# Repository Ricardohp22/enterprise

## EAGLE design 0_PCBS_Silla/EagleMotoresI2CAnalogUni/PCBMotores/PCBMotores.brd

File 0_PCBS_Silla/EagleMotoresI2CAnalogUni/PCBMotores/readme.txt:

PCB Motores - Estatus: Completo
----------------
-Control de motores con sabertooth salidas analógicas

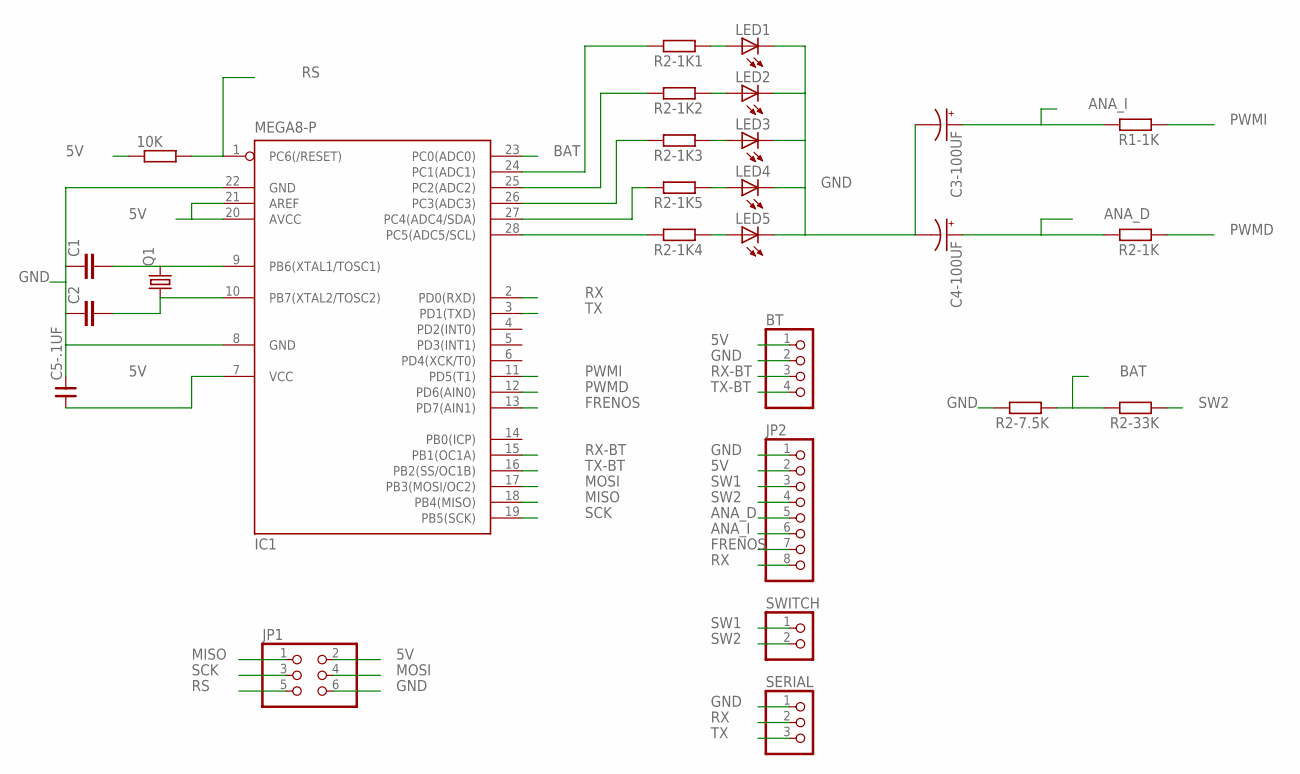
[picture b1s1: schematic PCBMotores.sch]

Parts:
10K: R-EU_0204/7; 0204/7
BT: PINHD-1X4; 1X04
C1, C2: C2.5/5; C2.5-5
C3-100UF, C4-100UF: CPOL-USE2-4; E2-4
C5-.1UF: CNP-C035-055X025; C035-055X025
IC1: MEGA8-P; DIL28-3
JP1: PINHD-2X3; 2X03
JP2: PINHD-1X8; 1X08
LED1, LED2, LED3, LED4, LED5: LED5MM
Q1: CRYSTALHC49S; HC49/S
R1-1K, R2-1K, R2-1K1, R2-1K2, R2-1K3, R2-1K4, R2-1K5, R2-7.5K, R2-33K: R-EU_0207/10; 0207/10
SERIAL: PINHD-1X3; 1X03
SWITCH: PINHD-1X2; 1X02

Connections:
5V: 10K.1, BT.1, C5-.1UF.1, IC1.7 (VCC), IC1.20 (AVCC), IC1.21 (AREF), JP1.2, JP2.2; also elsewhere on the board
ANA_D: C4-100UF.+, JP2.5, R2-1K.2; also elsewhere on the board
ANA_I: C3-100UF.+, JP2.6, R1-1K.2; also elsewhere on the board
BAT: IC1.23 (PC0(ADC0)), R2-7.5K.1, R2-33K.2
FRENOS: IC1.13 (PD7(AIN1)), JP2.7; also elsewhere on the board
GND: BT.2, C1.1, C2.1, C3-100UF.-, C4-100UF.-, C5-.1UF.2, IC1.8 (GND), IC1.22 (GND), JP1.6, JP2.1, LED1.K (C), LED2.K (C), LED3.K (C), LED4.K (C), LED5.K (C), R2-7.5K.2, SERIAL.1; also elsewhere on the board
MISO: IC1.18 (PB4(MISO)), JP1.1
MOSI: IC1.17 (PB3(MOSI/OC2)), JP1.4
unnamed: IC1.24 (PC1(ADC1)), R2-1K1.2
unnamed: IC1.25 (PC2(ADC2)), R2-1K2.2
unnamed: IC1.26 (PC3(ADC3)), R2-1K3.2
unnamed: C2.2, IC1.10 (PB7(XTAL2/TOSC2)), Q1.1
unnamed: C1.2, IC1.9 (PB6(XTAL1/TOSC1)), Q1.2
unnamed: IC1.27 (PC4(ADC4/SDA)), R2-1K5.2
unnamed: IC1.28 (PC5(ADC5/SCL)), R2-1K4.2
unnamed: LED1.A, R2-1K1.1
unnamed: LED2.A, R2-1K2.1
unnamed: LED3.A, R2-1K3.1
unnamed: LED4.A, R2-1K5.1
unnamed: LED5.A, R2-1K4.1
PWMD: IC1.12 (PD6(AIN0)), R2-1K.1
PWMI: IC1.11 (PD5(T1)), R1-1K.1
RS: 10K.2, IC1.1 (PC6(/RESET)), JP1.5
RX: IC1.2 (PD0(RXD)), JP2.8, SERIAL.2
RX-BT: BT.3, IC1.15 (PB1(OC1A))
SCK: IC1.19 (PB5(SCK)), JP1.3
SW1: JP2.3, SWITCH.1; also elsewhere on the board
SW2: JP2.4, R2-33K.1, SWITCH.2; also elsewhere on the board
TX: IC1.3 (PD1(TXD)), SERIAL.3
TX-BT: BT.4, IC1.16 (PB2(SS/OC1B))

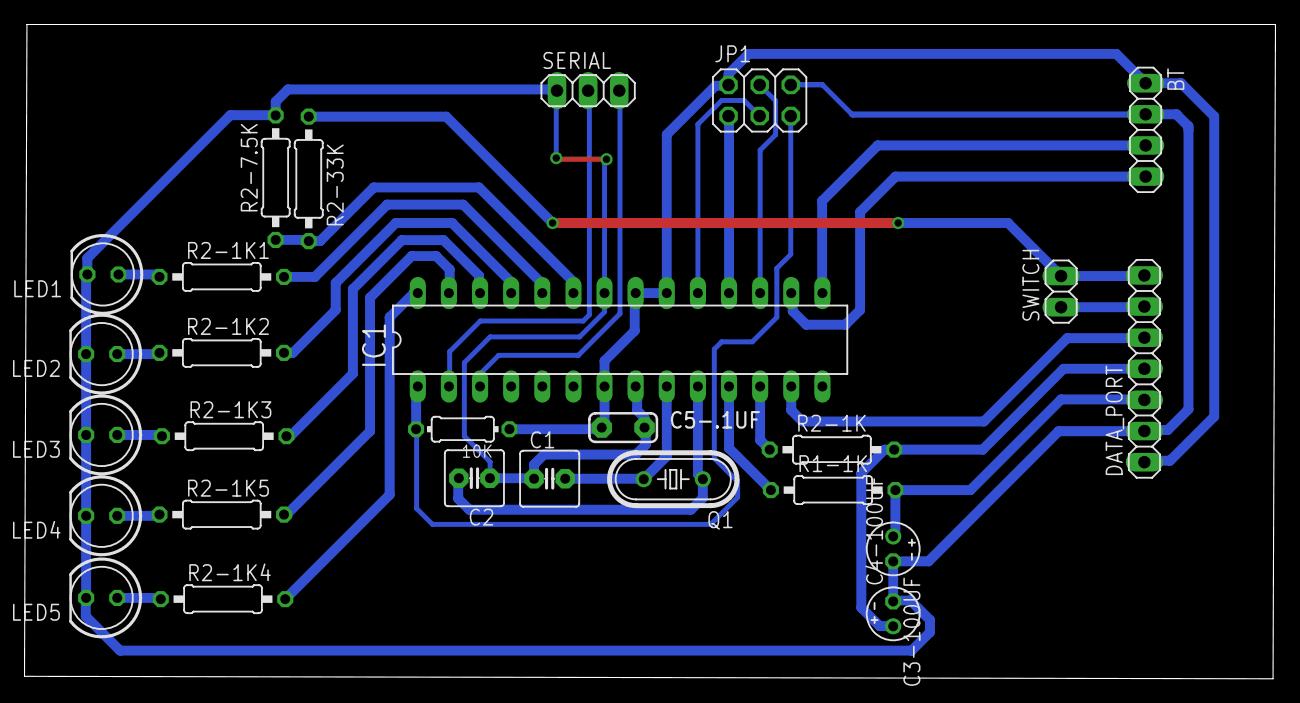
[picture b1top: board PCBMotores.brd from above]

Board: 2 copper layers, 102.1 x 53.4 mm, 27 parts (0 on the bottom side), 30 nets.

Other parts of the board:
DATA_PORT: 1X07

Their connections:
5V: DATA_PORT.1; also elsewhere on the board
ANA_D: DATA_PORT.4; also elsewhere on the board
ANA_I: DATA_PORT.3; also elsewhere on the board
FRENOS: DATA_PORT.5; also elsewhere on the board
GND: DATA_PORT.2; also elsewhere on the board
SW1: DATA_PORT.6; also elsewhere on the board
SW2: DATA_PORT.7; also elsewhere on the board

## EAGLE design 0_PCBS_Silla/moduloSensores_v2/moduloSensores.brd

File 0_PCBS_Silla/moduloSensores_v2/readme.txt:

PCB modulo de sensores v2 - Estatus: Completo
----------------
-Gestion de sensores de distancia y comunicacion con modulo de control
-integracion de resistencia pull-down

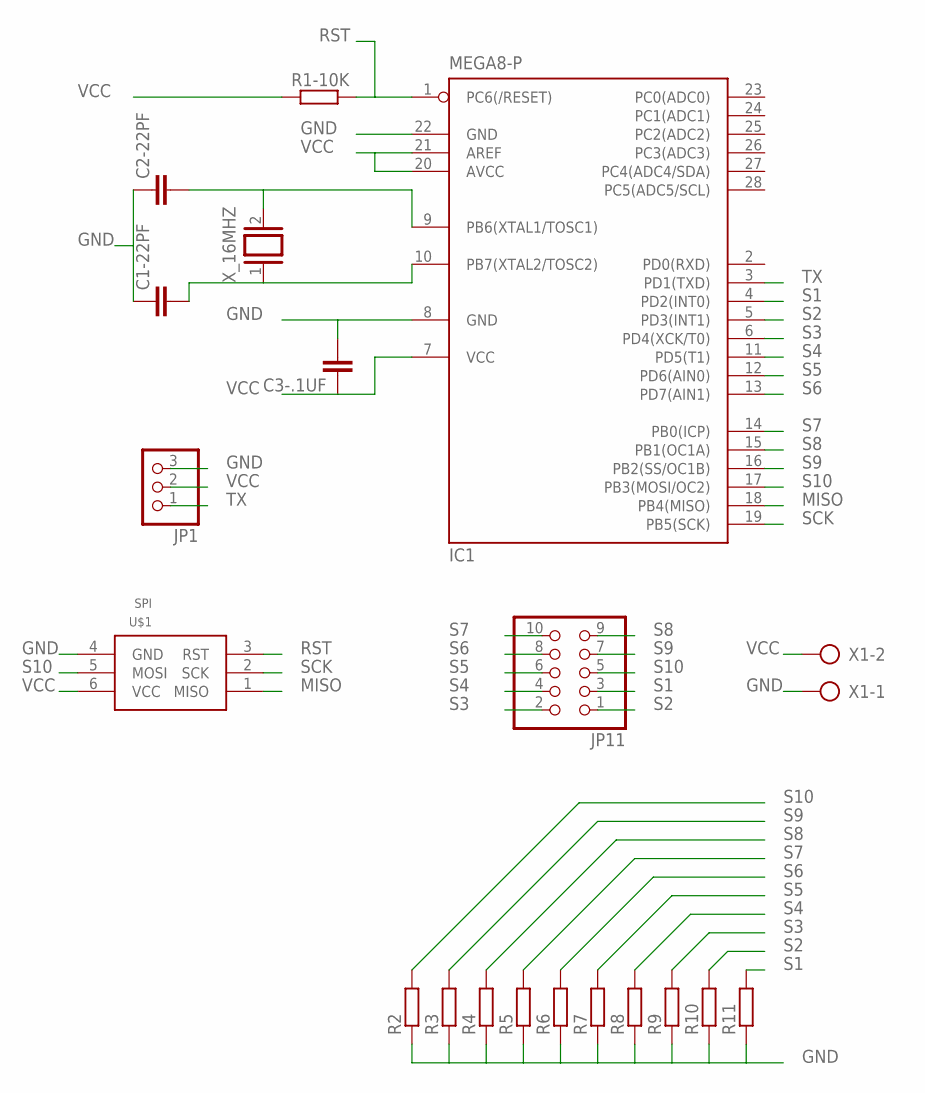
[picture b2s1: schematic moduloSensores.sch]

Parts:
C1-22PF, C2-22PF, C3-.1UF: C-EU050-025X075; C050-025X075
IC1: MEGA8-P; DIL28-3
JP1: PINHD-1X3; 1X03
JP11: PINHD-2X5; 2X05
R1-10K, R2, R3, R4, R5, R6, R7, R8, R9, R10, R11: R-EU_0204/7; 0204/7
U$1: SPI; HEAD-2X3
X1: AK500/2
X_16MHZ: XTAL/S; QS

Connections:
GND: C1-22PF.1, C2-22PF.1, C3-.1UF.2, IC1.8 (GND), IC1.22 (GND), JP1.3, R2.1, R3.1, R4.1, R5.1, R6.1, R7.1, R8.1, R9.1, R10.1, R11.1, U$1.4 (GND), X1.1
MISO: IC1.18 (PB4(MISO)), U$1.1 (MISO)
unnamed: C2-22PF.2, IC1.9 (PB6(XTAL1/TOSC1)), X_16MHZ.2
unnamed: C1-22PF.2, IC1.10 (PB7(XTAL2/TOSC2)), X_16MHZ.1
RST: IC1.1 (PC6(/RESET)), R1-10K.2, U$1.3 (RST)
S1: IC1.4 (PD2(INT0)), JP11.3, R11.2
S2: IC1.5 (PD3(INT1)), JP11.1, R10.2
S3: IC1.6 (PD4(XCK/T0)), JP11.2, R9.2
S4: IC1.11 (PD5(T1)), JP11.4, R8.2
S5: IC1.12 (PD6(AIN0)), JP11.6, R7.2
S6: IC1.13 (PD7(AIN1)), JP11.8, R6.2
S7: IC1.14 (PB0(ICP)), JP11.10, R5.2
S8: IC1.15 (PB1(OC1A)), JP11.9, R4.2
S9: IC1.16 (PB2(SS/OC1B)), JP11.7, R3.2
S10: IC1.17 (PB3(MOSI/OC2)), JP11.5, R2.2, U$1.5 (MOSI)
SCK: IC1.19 (PB5(SCK)), U$1.2 (SCK)
TX: IC1.3 (PD1(TXD)), JP1.1
VCC: C3-.1UF.1, IC1.7 (VCC), IC1.20 (AVCC), IC1.21 (AREF), JP1.2, R1-10K.1, U$1.6 (VCC), X1.2

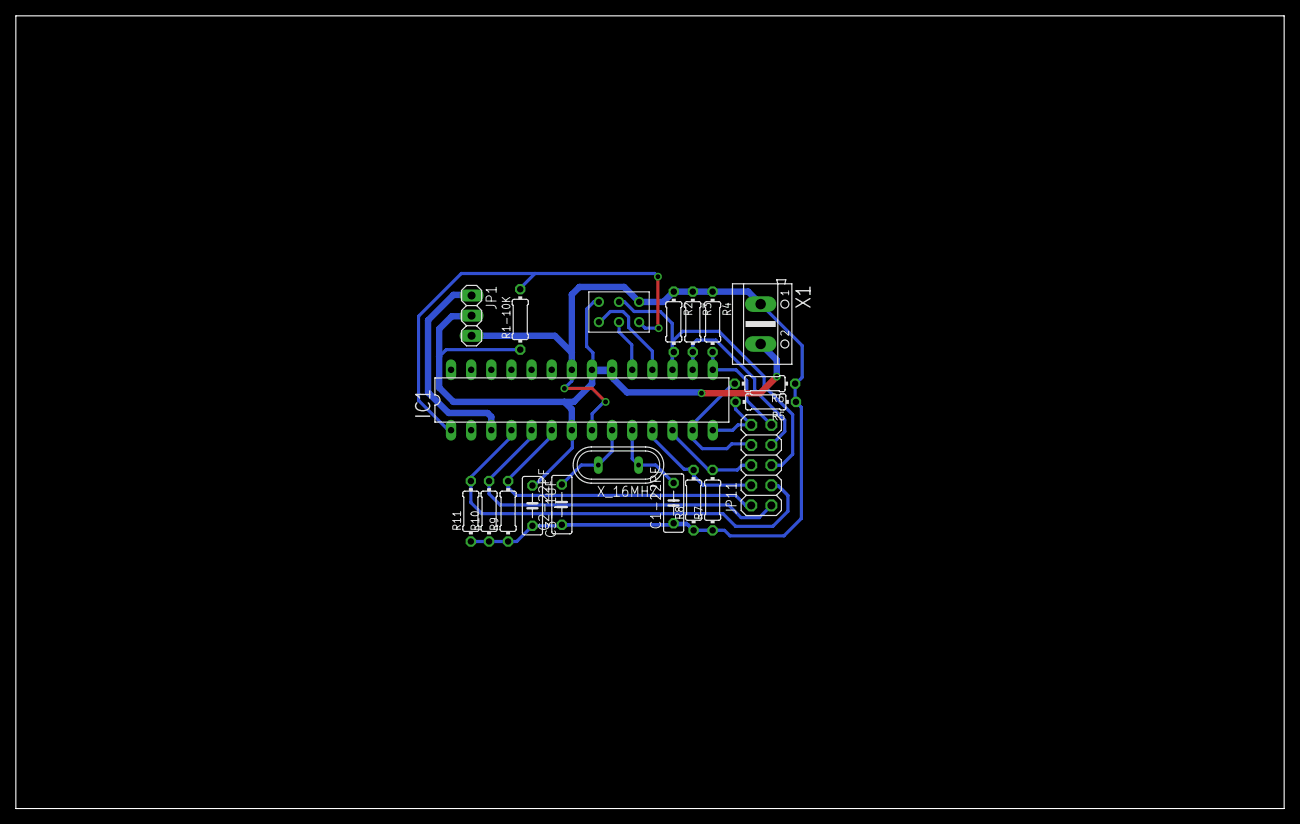
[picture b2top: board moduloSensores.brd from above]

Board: 2 copper layers, 160.0 x 100.0 mm, 20 parts (0 on the bottom side), 18 nets.

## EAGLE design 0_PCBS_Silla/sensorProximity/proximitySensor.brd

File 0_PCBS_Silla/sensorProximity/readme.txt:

ProximitySensor - Estatus: completo
----------------
-Control de sensor ultrasónico con indicador visual y auditivo

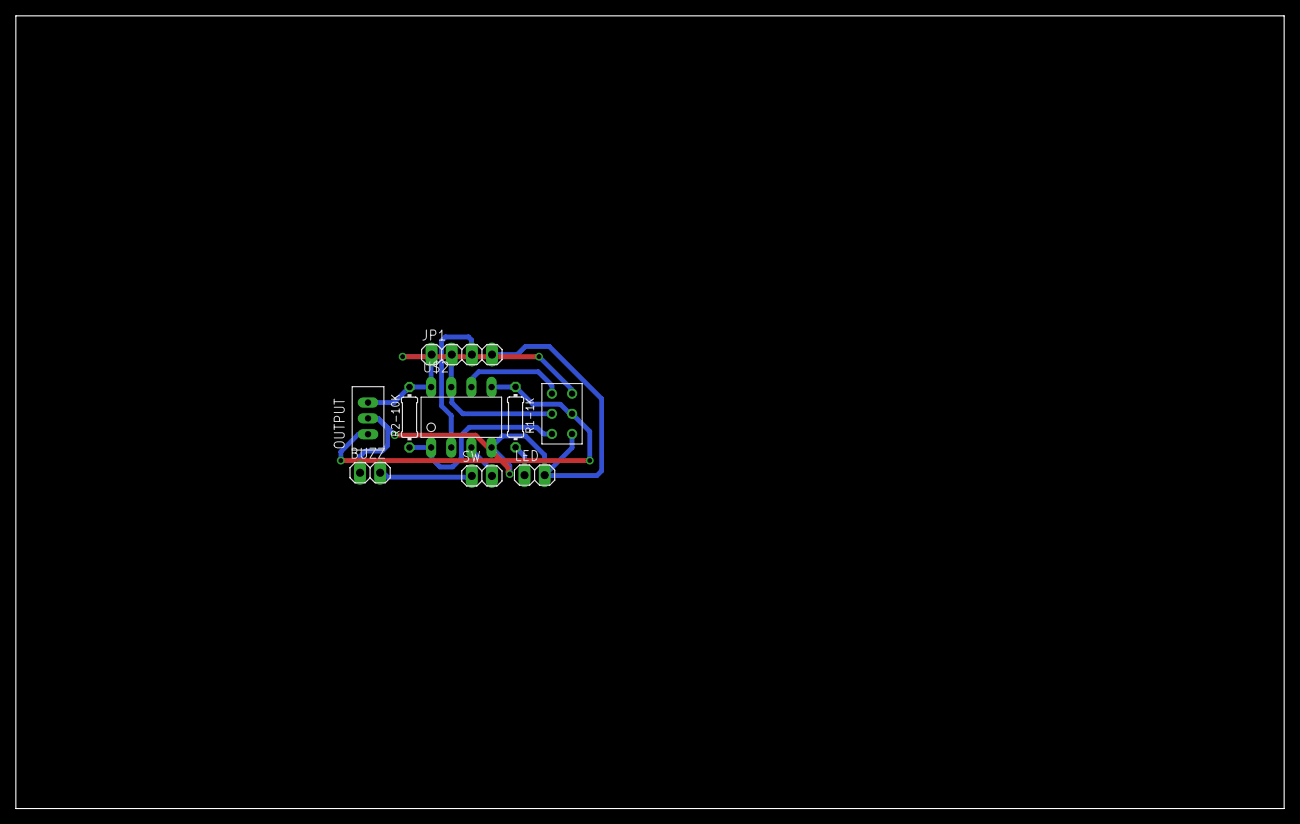
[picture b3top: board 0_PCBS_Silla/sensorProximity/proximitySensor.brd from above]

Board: 2 copper layers, 160.0 x 100.0 mm, 9 parts (0 on the bottom side), 10 nets.

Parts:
BUZZ: 1X02
JP1: 1X04
LED: 1X02
OUTPUT: PINH_1X3; PINHEADER
R1-1K, R2-10K: 0204/7
SW: 1X02
U$1: SPI; HEAD-2X3
U$2: ATTINY85; DIL-8

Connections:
ECHO: JP1.3, U$2.2
GND: BUZZ.1, JP1.4, LED.2, OUTPUT.2, U$1.4, U$2.4
MISO: U$1.1, U$2.6
unnamed: SW.2, U$2.3
unnamed: LED.1, R1-1K.2
unnamed: BUZZ.2, SW.1
OUT: OUTPUT.1, R1-1K.1, U$1.5, U$2.5
RESET: R2-10K.1, U$1.3, U$2.1
TRIG: JP1.2, U$1.2, U$2.7
VCC: JP1.1, OUTPUT.3, R2-10K.2, U$1.6, U$2.8

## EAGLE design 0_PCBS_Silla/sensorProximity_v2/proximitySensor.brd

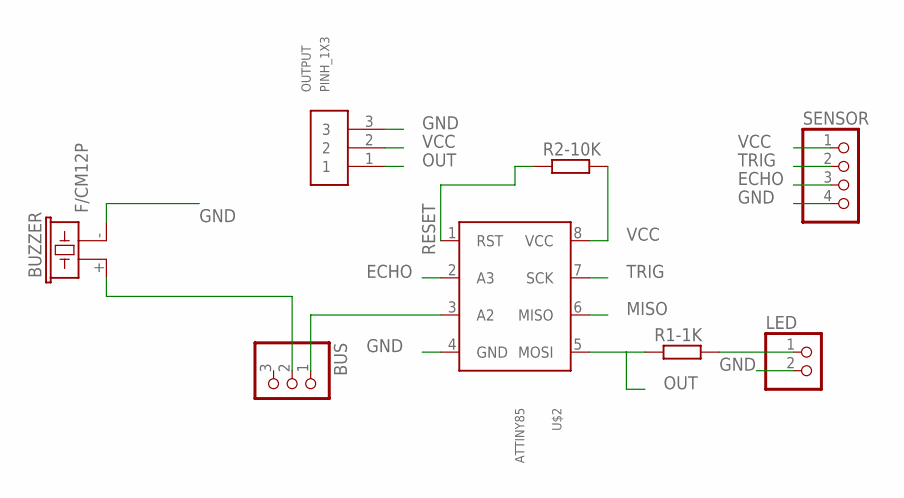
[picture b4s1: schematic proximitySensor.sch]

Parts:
BUS: PINHD-1X3; 1X03
BUZZER: F/CM12P
LED: PINHD-1X2; 1X02
OUTPUT: PINH_1X3; PINHEADER
R1-1K, R2-10K: R-EU_0204/7; 0204/7
SENSOR: PINHD-1X4; 1X04
U$2: ATTINY85; DIL-8

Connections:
ECHO: SENSOR.3, U$2.2 (A3)
GND: BUZZER.- (2), LED.2, OUTPUT.3, SENSOR.4, U$2.4 (GND)
MISO: U$2.6 (MISO)
unnamed: BUS.1, U$2.3 (A2)
unnamed: LED.1, R1-1K.2
unnamed: BUS.2, BUZZER.+ (1)
OUT: OUTPUT.1, R1-1K.1, U$2.5 (MOSI)
RESET: R2-10K.1, U$2.1 (RST)
TRIG: SENSOR.2, U$2.7 (SCK)
VCC: OUTPUT.2, R2-10K.2, SENSOR.1, U$2.8 (VCC)

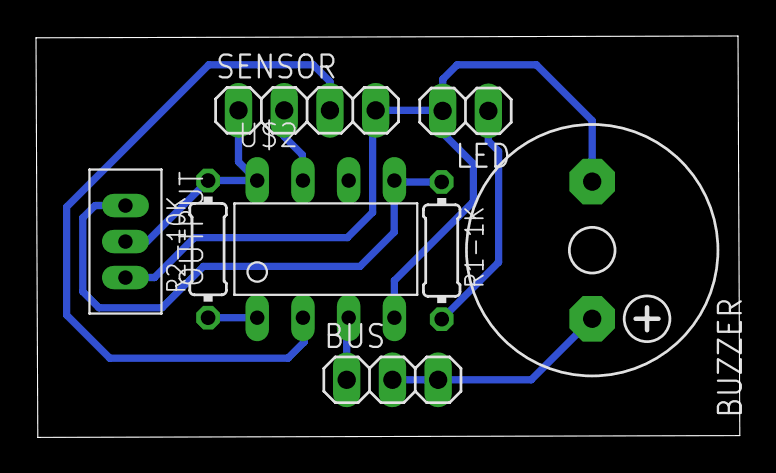
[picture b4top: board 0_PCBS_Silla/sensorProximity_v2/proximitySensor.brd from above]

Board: 2 copper layers, 39.1 x 22.3 mm, 8 parts (0 on the bottom side), 9 nets.

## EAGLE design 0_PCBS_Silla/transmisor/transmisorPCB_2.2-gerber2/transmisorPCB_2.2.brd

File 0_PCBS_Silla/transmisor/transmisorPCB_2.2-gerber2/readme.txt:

TransmisorPCB_2.2 - Estatus: En progreso
----------------
-Lectura de mp5060 y envio de posicion por bluetooth
-Reduccion de puertos
-Incorporación de boton de offset
-incorporacion de buzzer

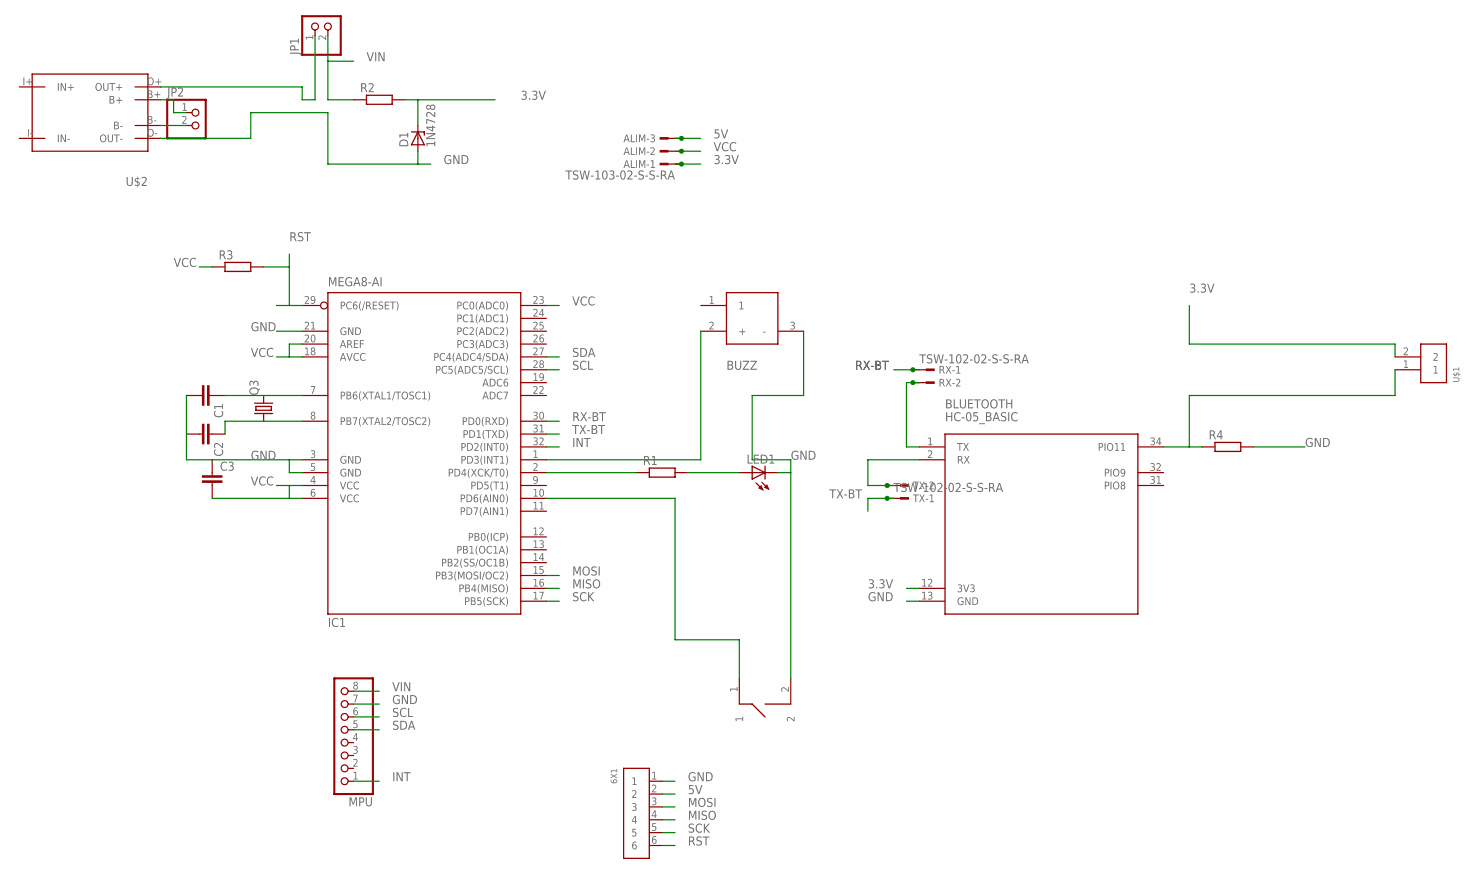
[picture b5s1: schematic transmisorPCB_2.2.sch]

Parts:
6X1: PINHEAD_1X6; PINHEAD_125_1X6
ALIM: TSW-103-02-S-S-RA
BLUETOOTH: HC-05_BASIC; BLUETOOTH_SMD
BUZZ: SM05ET02A
C1, C2, C3: C-EUC0402K; C0402K
D1: 1N4728; DO41Z10
IC1: MEGA8-AI; TQFP32-08
JP1, JP2: PINHD-1X2; 1X02
LED1: LEDCHIPLED-0603-TTW; CHIPLED-0603-TTW
MPU: PINHD-1X8; 1X08
PUSH: PUSH_SMD
Q3: CRYSTALHC49U70; HC49U70
R1, R3, R4: R-EU_M1206; M1206
R2: R-EU_R2512; R2512
RX: TSW-102-02-S-S-RA
TX: TSW-102-02-S-S-RA
U$1: CP150_1X2
U$2: TP4056

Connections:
3.3V: ALIM.1, BLUETOOTH.12 (3V3), D1.C, R2.2, U$1.2
5V: 6X1.2, ALIM.3
GND: 6X1.1, BLUETOOTH.13 (GND), BUZZ.3 (-), C1.2, C2.2, C3.1, D1.A, IC1.3 (GND), IC1.5 (GND), IC1.21 (GND), LED1.C@1 (C), MPU.7, PUSH.2, R4.2, U$2.O- (OUT-)
INT: IC1.32 (PD2(INT0)), MPU.1
MISO: 6X1.4, IC1.16 (PB4(MISO))
MOSI: 6X1.3, IC1.15 (PB3(MOSI/OC2))
unnamed: JP1.1, U$2.O+ (OUT+)
unnamed: BLUETOOTH.2 (RX), TX.2
unnamed: C1.1, IC1.7 (PB6(XTAL1/TOSC1)), Q3.2
unnamed: C2.1, IC1.8 (PB7(XTAL2/TOSC2)), Q3.1
unnamed: BUZZ.2 (+), IC1.1 (PD3(INT1))
unnamed: IC1.2 (PD4(XCK/T0)), R1.1
unnamed: JP2.2, U$2.B-
unnamed: BLUETOOTH.1 (TX), RX.2
unnamed: JP2.1, U$2.B+
unnamed: LED1.A@1 (A), R1.2
unnamed: BLUETOOTH.34 (PIO11), R4.1, U$1.1
unnamed: IC1.10 (PD6(AIN0)), PUSH.1
RST: 6X1.6, IC1.29 (PC6(/RESET)), R3.2
RX-BT: IC1.30 (PD0(RXD)), RX.1
SCK: 6X1.5, IC1.17 (PB5(SCK))
SCL: IC1.28 (PC5(ADC5/SCL)), MPU.6
SDA: IC1.27 (PC4(ADC4/SDA)), MPU.5
TX-BT: IC1.31 (PD1(TXD)), TX.1
VCC: ALIM.2, C3.2, IC1.4 (VCC), IC1.6 (VCC), IC1.18 (AVCC), IC1.20 (AREF), IC1.23 (PC0(ADC0)), R3.1
VIN: JP1.2, MPU.8, R2.1

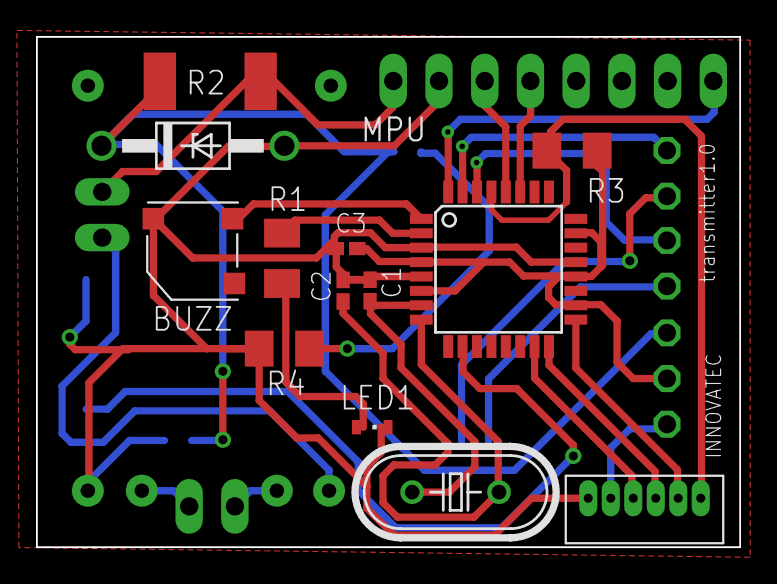
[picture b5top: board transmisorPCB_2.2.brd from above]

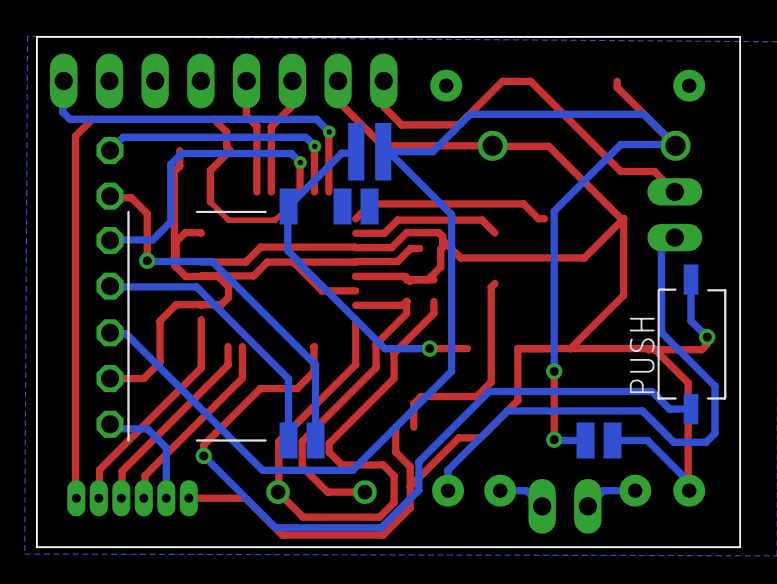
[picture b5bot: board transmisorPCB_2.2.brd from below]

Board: 2 copper layers, 39.1 x 28.4 mm, 23 parts (3 on the bottom side), 26 nets.

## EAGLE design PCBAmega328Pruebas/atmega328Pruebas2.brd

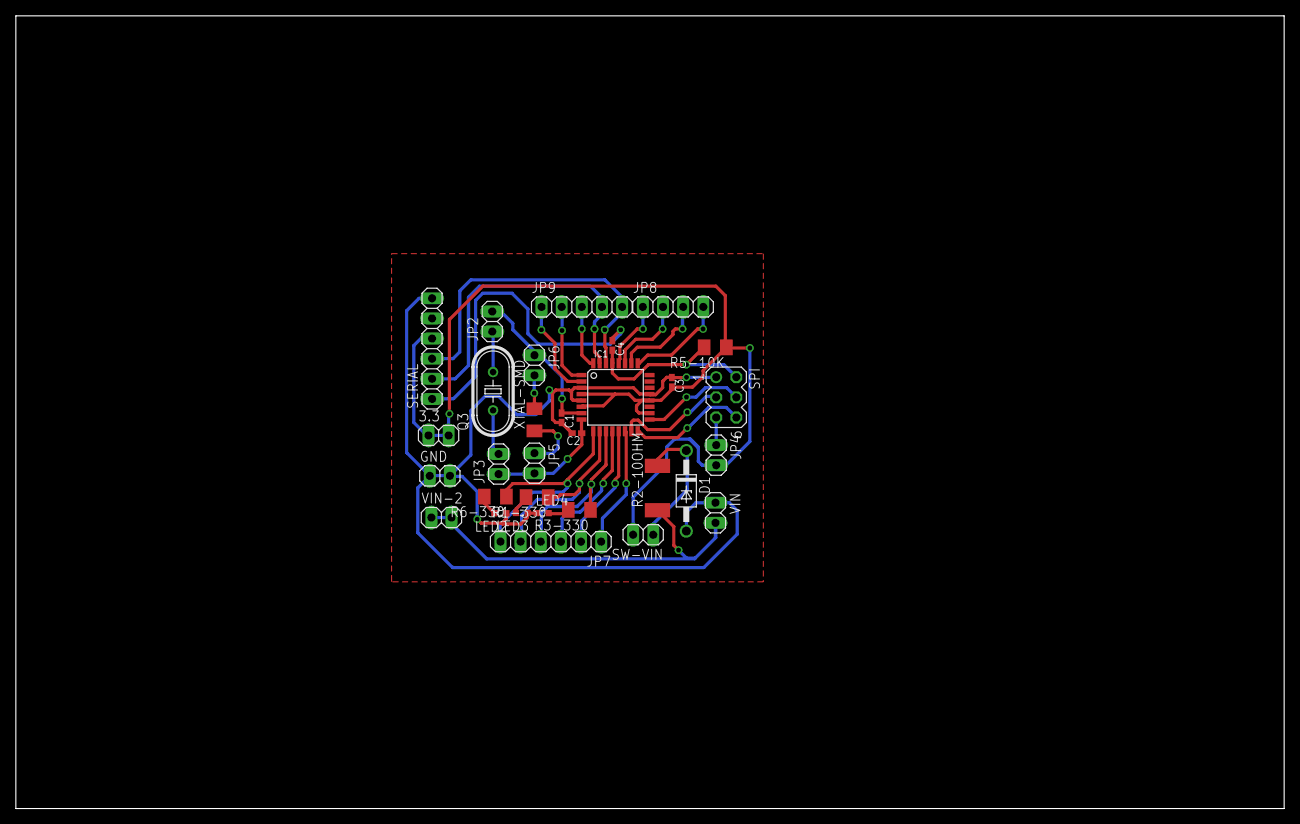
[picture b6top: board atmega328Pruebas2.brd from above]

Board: 2 copper layers, 160.0 x 100.0 mm, 31 parts (0 on the bottom side), 34 nets.

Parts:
3.3: 1X02
C1, C2, C3, C4: C0402K
D1: 1N4728; DO41Z10
GND: 1X02
IC1: MEGA8-AI; TQFP32-08
JP2, JP3, JP4, JP5, JP6: 1X02
JP7: 1X06
JP8: 1X04
JP9: 1X05
LED2, LED3, LED4: LED_SML0603
Q3: HC49U70
R1-330, R3-330, R5-10K, R6-330: M1206
R2-10OHM: R2512
SERIAL: 1X06
SPI: MA03-2
SW-VIN: 1X02
VIN: 1X02
VIN-2: 1X02
XTAL-SMD: M1206

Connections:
3.3V: 3.3.1, 3.3.2, C3.2, IC1.4, IC1.6, IC1.18, IC1.20, JP4.2, R5-10K.1, SERIAL.4, SW-VIN.2
B0: IC1.12, JP7.3
B1: IC1.13, JP7.2
B2: IC1.14, JP7.1
C2: IC1.25, JP8.4
C3: IC1.26, JP8.3
C4: IC1.27, JP8.2
C5: IC1.28, JP8.1
D2: IC1.32, JP9.3
D3: IC1.1, JP9.2
D4: IC1.2, JP9.1
D5: IC1.9, JP7.6, R6-330.1
D6: IC1.10, JP7.5, R1-330.1
D7: IC1.11, JP7.4, R3-330.1
DTR: C4.1, SERIAL.1
GND: C1.2, C2.2, C3.1, D1.A, GND.1, GND.2, IC1.3, IC1.5, IC1.21, LED2.C, LED3.C, LED4.C, SERIAL.6, SPI.1, VIN.1
MISO: IC1.16, SPI.6
MOSI: IC1.15, SPI.3
unnamed: D1.C, R2-10OHM.2, SW-VIN.1
unnamed: R2-10OHM.1, VIN.2, VIN-2.1, VIN-2.2
unnamed: JP2.1, Q3.2
unnamed: JP3.2, Q3.1
unnamed: JP5.1, XTAL-SMD.1
unnamed: JP6.2, XTAL-SMD.2
unnamed: C1.1, IC1.7, JP2.2, JP6.1
unnamed: C2.1, IC1.8, JP3.1, JP5.2
unnamed: LED2.A, R6-330.2
unnamed: LED3.A, R1-330.2
unnamed: LED4.A, R3-330.2
unnamed: JP4.1, SPI.5
RST: C4.2, IC1.29, R5-10K.2, SPI.2
RX: IC1.30, JP9.5, SERIAL.3
SCK: IC1.17, SPI.4
TX: IC1.31, JP9.4, SERIAL.2
